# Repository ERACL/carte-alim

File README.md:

Carte d'alimentation
====================

Carte d'alimentation du robot - Contient la CAO KiCAD de la carte

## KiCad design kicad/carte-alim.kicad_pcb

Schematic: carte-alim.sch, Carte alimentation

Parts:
C1, C3, C5: 100n; C_Rect_L7.0mm_W3.5mm_P2.50mm_P5.00mm
C2, C4, C6: 100u; CP_Radial_D10.0mm_P2.50mm_P5.00mm
D1: YELLOW; LED_D3.0mm
D2: RED; LED_D3.0mm
D3: ORANGE; LED_D3.0mm
J1, J2, J3, J4, J5, J6, J7, J8, J9, J10: PWR_OUT; Molex_MiniFit-JR-5569-04A2_2x02x4.20mm_Angled
P1, P2, P3, P5: MECA; MountingHole_3.2mm_M3_Pad
P4: PILES; Molex_MiniFit-JR-5569-02A2_2x01x4.20mm_Angled
P6: MASSE; Pin_Header_Straight_1x08_Pitch2.54mm
P7: +5V; Pin_Header_Straight_1x08_Pitch2.54mm
P8: +3.3V; Pin_Header_Straight_1x08_Pitch2.54mm
R1: 680; R_Axial_DIN0207_L6.3mm_D2.5mm_P7.62mm_Horizontal
R2, R3: 470; R_Axial_DIN0207_L6.3mm_D2.5mm_P7.62mm_Horizontal
U1: LM 1117 3.3; TO-220-3_Horizontal_Radiat
U2: OKI 78SR 5; TO-220-3_Horizontal_Radiat

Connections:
+3V3: C1.1, C2.1, J1.3, J2.3, J3.3, J4.3, J5.3, J6.3, J7.3, J8.3, J9.3, J10.3, P8.1, P8.2, P8.3, P8.4, P8.5, P8.6, P8.7, P8.8, R3.2, U1.2
+5V: C5.1, C6.1, J1.2, J2.2, J3.2, J4.2, J5.2, J6.2, J7.2, J8.2, J9.2, J10.2, P7.1, P7.2, P7.3, P7.4, P7.5, P7.6, P7.7, P7.8, R2.2, U2.3
+BATT: C3.1, C4.1, J1.4, J2.4, J3.4, J4.4, J5.4, J6.4, J7.4, J8.4, J9.4, J10.4, P4.2, R1.2, U1.3, U2.1
GND: C1.2, C2.2, C3.2, C4.2, C5.2, C6.2, D1.1, D2.1, D3.1, J1.1, J2.1, J3.1, J4.1, J5.1, J6.1, J7.1, J8.1, J9.1, J10.1, P4.1, P6.1, P6.2, P6.3, P6.4, P6.5, P6.6, P6.7, P6.8, U1.1, U2.2
unnamed: D1.2, R1.1
unnamed: D2.2, R2.1
unnamed: D3.2, R3.1

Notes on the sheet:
Trous fixation
Témoins d'alimentation
Conversion +3.3V
Connecteurs pour branchement vers autres cartes
Conversion +5V
Bus d'alimentation
Convensions couleurs : 1 - Noir : masse 2 - Rouge : +5V 3 - Orange : +3.3V 4 - Jaune : BATT
Branchement batteries

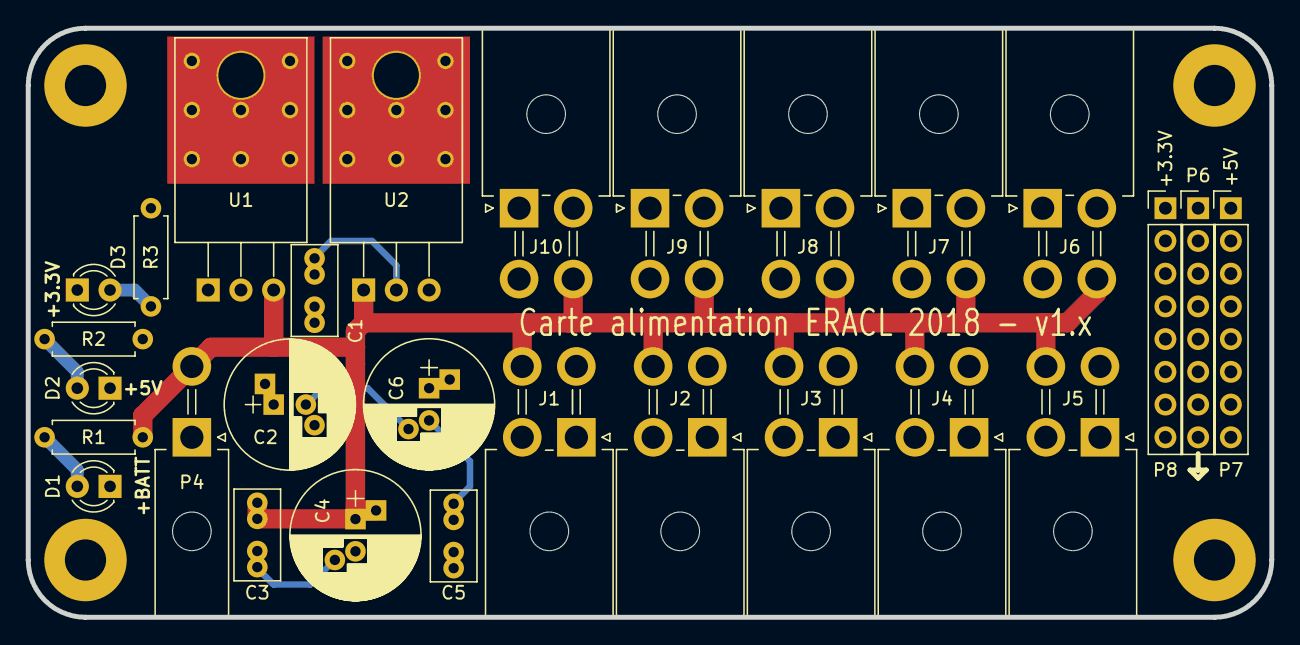
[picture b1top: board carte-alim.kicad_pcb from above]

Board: 4 copper layers, 96.5 x 45.7 mm, 32 parts (0 on the bottom side), 7 nets.

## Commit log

2018-01-30 Mise en forme du fichier README
2018-02-10 Changement des connecteurs SIL pour des connecteurs coudés
2018-02-10 Modification du typon suivant recommandations PLJ
2018-02-10 Ajout de modules pour les pins avec détrompeurs
2018-02-10 Correction empreinte régulateur 3.3V
2018-02-10 Rajout de pins d'alimentation et modification du typon en conséquence
2018-02-10 Ajout de trous de fixation
2018-02-10 Rajout plans de masse
2018-02-10 Initial commit carte alim
2018-02-10 Composants valués + rajout condos polarisés en sortie des régulateurs
2018-02-10 Rajout infos sérigraphie
2018-02-10 Renommage des fichiers selon les bonnes conventions de nommage
2018-02-10 Validation et nettoyage du schéma
2018-02-10 Ajout de la librairie de modules EPSA au projet
2018-02-10 Association composants
2018-02-10 Mise à jour du format du typon
2018-02-10 Utilisation de diodes avec un pas de 10mm au lieu de 7,5mm
2018-02-11 Mise en qualité du typon
2018-02-11 Schématique avec connecteurs multi-tensions
2018-02-11 Réalisation du typon avec connecteurs Mini-Fit
2018-02-11 Mise à jour de la version dans les cartouches et la sérigraphie
2018-02-11 Ignore dossier export KiCAD
2018-02-11 Utilisation diamètre de perçage standard pour les vias du radiateur
2018-02-20 Reprise du schéma pour corriger bug d'affichage
